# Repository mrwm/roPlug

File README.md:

# roPlug
ATMega32U4 with a male USB plug.

***

- [KiCAD Pictures](#KiCAD-Pictures)
- [PCB Pictures](#PCB-Pictures)

Extra parts - post pcba:

- EC05E1220203 - 2.7mm low profile encoder (incompatible) | [mouser](https://www.mouser.com/ProductDetail/Alps-Alpine/EC05E1220203?qs=%2Fha2pyFadujxX3lsKV%2F2v0IdfHtW%2FTX9iJN7eVGbwjXvhMXGXqwokw%3D%3D) | [SnapEDA](https://www.snapeda.com/parts/EC05E1220203/ALPS/view-part/157580/?ref=search&t=EC05E1220203) | [datasheet](https://www.mouser.com/datasheet/2/15/EC05E-1370804.pdf)
- EVQ-VVD00203B - 2.2mm low profile encoder (incompatible) | [mouser](https://www.mouser.com/ProductDetail/Panasonic/EVQ-VVD00203B/?qs=tfZGHB2PWd3U%2F4kR6m1kxw%3D%3D) | [datasheet](https://www.mouser.com/datasheet/2/315/ATC0000CE22-531565.pdf)
- 292V1X24A - 3.8mm ring encoder (incompatible) | [mouser](https://www.mouser.com/ProductDetail/CTS-Electronic-Components/292V1X24A?qs=OlC7AqGiEDkLZ8geXnuzig%3D%3D) | [datasheet](https://www.mouser.com/datasheet/2/96/ctsc_s_a0010171236_1-2265081.pdf)
- EC12E1220301 - 4.5mm encoder | [mouser](https://www.mouser.com/ProductDetail/688-EC12E1220301) | [datasheet](https://www.mouser.de/datasheet/2/15/EC12E-1370769.pdf)

***

## KiCAD Pictures

***

## PCB Pictures

Note: The Molex USB C connector reaches a bit past the solder masks, but
shouldn't affect the assembly process. (Fig. 1)

*Fig. 1*

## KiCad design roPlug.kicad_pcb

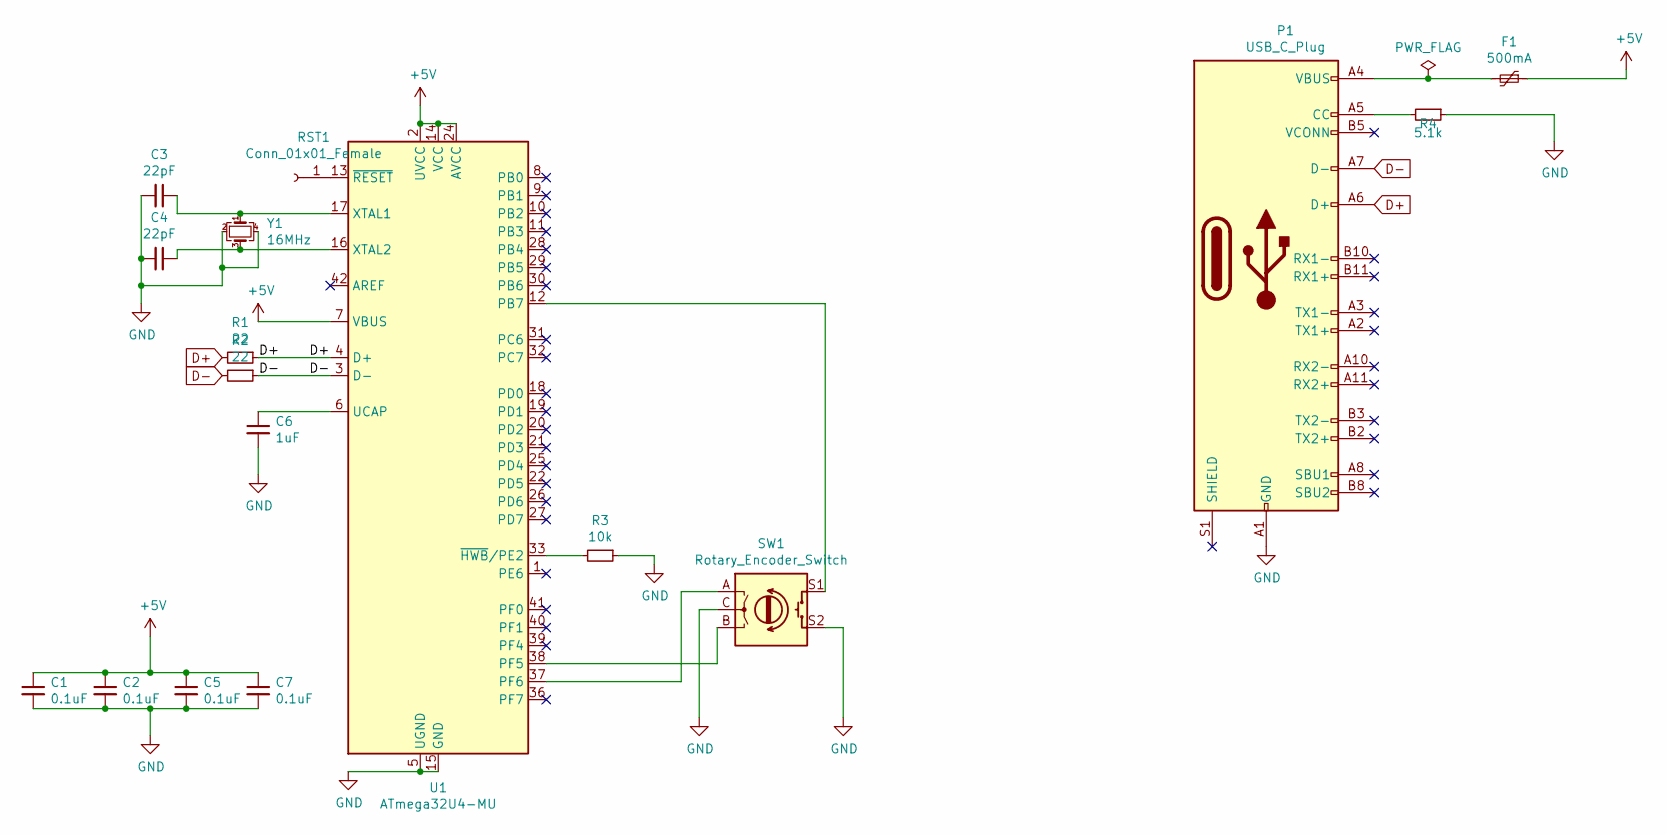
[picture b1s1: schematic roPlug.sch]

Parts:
C1, C2, C5, C7: 0.1uF; C_0603_1608Metric
C3, C4: 22pF; C_0603_1608Metric
C6: 1uF; C_0603_1608Metric
F1: 500mA; Fuse_1206_3216Metric
P1: USB_C_Plug; USB_C_Plug_Molex_105444
R1, R2: 22; R_0603_1608Metric
R3: 10k; R_0603_1608Metric
R4: 5.1k; R_0603_1608Metric
RST1: Conn_01x01_Female; PinSocket_1x01_P2.54mm_Vertical
SW1: Rotary_Encoder_Switch; RotaryEncoder_Alps_EC11E-Switch_Vertical_H20mm_NS
U1: ATmega32U4-MU; QFN-44-1EP_7x7mm_P0.5mm_EP5.2x5.2mm
Y1: 16MHz; Crystal_SMD_Abracon_ABM3B-4Pin_5.0x3.2mm

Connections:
+5V: C1.1, C2.1, C5.1, C7.1, F1.1, U1.2 (UVCC), U1.7 (VBUS), U1.14 (VCC), U1.24 (AVCC), U1.34 (VCC), U1.44 (AVCC)
D+: P1.A6 (D+), R1.1, R1.2, U1.4 (D+)
D-: P1.A7 (D-), R2.1, R2.2, U1.3 (D-)
GND: C1.2, C2.2, C3.2, C4.2, C5.2, C6.2, C7.2, P1.A1 (GND), P1.A12 (GND), P1.B1 (GND), P1.B12 (GND), R3.1, R4.1, SW1.C, SW1.S2, U1.5 (UGND), U1.15 (GND), U1.23 (GND), U1.35 (GND), U1.43 (GND), U1.45 (GND), Y1.2, Y1.4
unnamed: C3.1, U1.17 (XTAL1), Y1.1
unnamed: C4.1, U1.16 (XTAL2), Y1.3
unnamed: C6.1, U1.6 (UCAP)
unnamed: F1.2, P1.A4 (VBUS), P1.A9 (VBUS), P1.B4 (VBUS), P1.B9 (VBUS)
unnamed: P1.A5 (CC), R4.2
unnamed: R3.2, U1.33 (~HWB~/PE2)
unnamed: RST1.1, U1.13 (~RESET)
unnamed: SW1.A, U1.37 (PF6)
unnamed: SW1.B, U1.38 (PF5)
unnamed: SW1.S1, U1.12 (PB7)

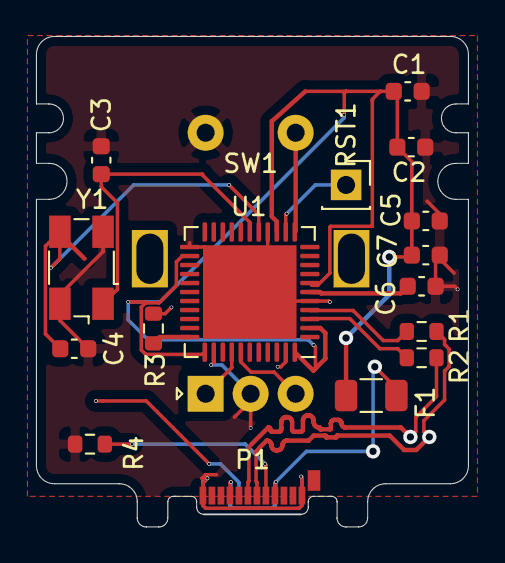
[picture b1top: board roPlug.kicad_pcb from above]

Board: 2 copper layers, 24.0 x 27.2 mm, 17 parts (0 on the bottom side), 14 nets.

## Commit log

2021-10-05 ignore misc folder
2021-10-06 ignore files generated for PCB creation
2021-10-06 add license
2021-10-06 change license link to actual license with content
2021-10-06 add Kicad files
2021-10-06 remove vias that are under pads
2021-10-07 update gerber exports to reflect via change
2021-10-07 add links for parts to get after pcba
2021-10-07 start adding gerber files to git
2021-10-07 change edgemount usb plug to sidemount due to supply issues with pcba
2021-10-08 add jlcpcb style bom for an estimate
2021-10-12 connect the unconnected ground pins on the usb plug
2021-10-12 update gerber files to reflect pcb changes
2021-10-22 update reference line to 30mm (basically the size of a framework expansion card).
2021-10-22 update readme and add pcb image
2021-10-22 Update README description
2021-10-22 format
2021-10-22 add screenshots & add step file for rotary encoder and fix file path for the crystal
2021-10-22 add images to readme
2021-10-23 add more connection to ground
2021-10-23 remove 3d model of ground pin
2021-10-23 rotate silk text of rst and add pre-final photos of PCB
2021-10-23 add formatted bom
2021-10-24 format README and add pictures
2021-10-24 change the edgecuts to be the same as the framework expansion cards
2021-10-24 fix up footprints hanging off the sides of the cut
2021-10-25 fix pcb wiring and update readme for laternative parts
2021-10-26 update bom to unclude mfg#
2021-10-27 add another rotary encoder option
2021-10-27 ignore dolphin files
2021-10-29 remove gerber & fix capacitors bad wiring
2021-10-29 add part prices from pcbway
2021-11-11 update schematics and fix USB-C circuitry for host detection
